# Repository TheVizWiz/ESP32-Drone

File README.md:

# ESP32 - Drone

### A Drone, Controller, and Flight Software, based on the popular ESP32 Microcontroller architecture.

## Current State
- Drone:  CAD model has been finalized and printed, as shown below. RF24 modules have been tested at distance, and motors and batteries have been mounted.
- Controller: PCB design is underway using multiplexers to extend ESP32 capabilities to more GPIO pins. RF24 module is being integrated, as well as battery circuitry.

### Drone Model

### PCB Schematic

## Overview
This is an ESP32-based from-scratch Drone project, meant to help learn the fundamentals of CAD, PCB design, control system software, as well as utilize the C++ programming language for high levels of multithreaded efficiency and performance. The Drone is built on a 4S cell system (14.8V), with 2200Kv motors (I would recommend going with a lower Kv value if you are reproducing this project, as that will be more efficient; I used what was on hand), and 10" propellers. It is designed to carry its own weight as well as a payload of ~1kg (2.2lb). 

## Project Objectives

### Drone
- Use Autodesk Inventor to design and 3D print a custom Drone body, built for carrying heavy weight (25+ kg).
- Utilize RF24 radio modules, as well as MPU6050 sensors, to build a real-time multithreaded flight control system, using PID control system algorithms.
- Create modular systems that allow for plug-and-play extension systems (eg. a payload-dropping and sensing system, as well as a front-mounted camera gimbal.)
- Build error-handling systems that allow for the easy handling of exception scenarios, such as loss of network signal or missed packets.
- Architecture system for Payload Acknowledge based telemetry, for use with flight telemetry / analysis software.

### Controller
- Use a secondary ESP32 system to measure input signals and relay to drone with RF24 modules.
- Utilize 74HC4051 ICs for breaking out signals, allowing for multiple expansion ports in the controller.
- Design and print controller body that allows for easy battery replacement and management, as well as easy access to controller ports for software updates. hook up GPIO_0 for easy boot access, as well as EN pin for reboots.

### Flight Software
- Use ElectronJS, ReactJS, and Victory Charts to create real-time telemetry for use on a desktop system.
- Build a Wifi-based connectivity system to relay information from drone to controller, package information, and then send asynchronously from controller to the host desktop system.
- Allow for multiple running systems and modes (sensing, graphs, console), as well as for reading data instead of only parsing from the drone. Further, use OpenGL and WebGL to render a 3D canvas view of the drone in flight.

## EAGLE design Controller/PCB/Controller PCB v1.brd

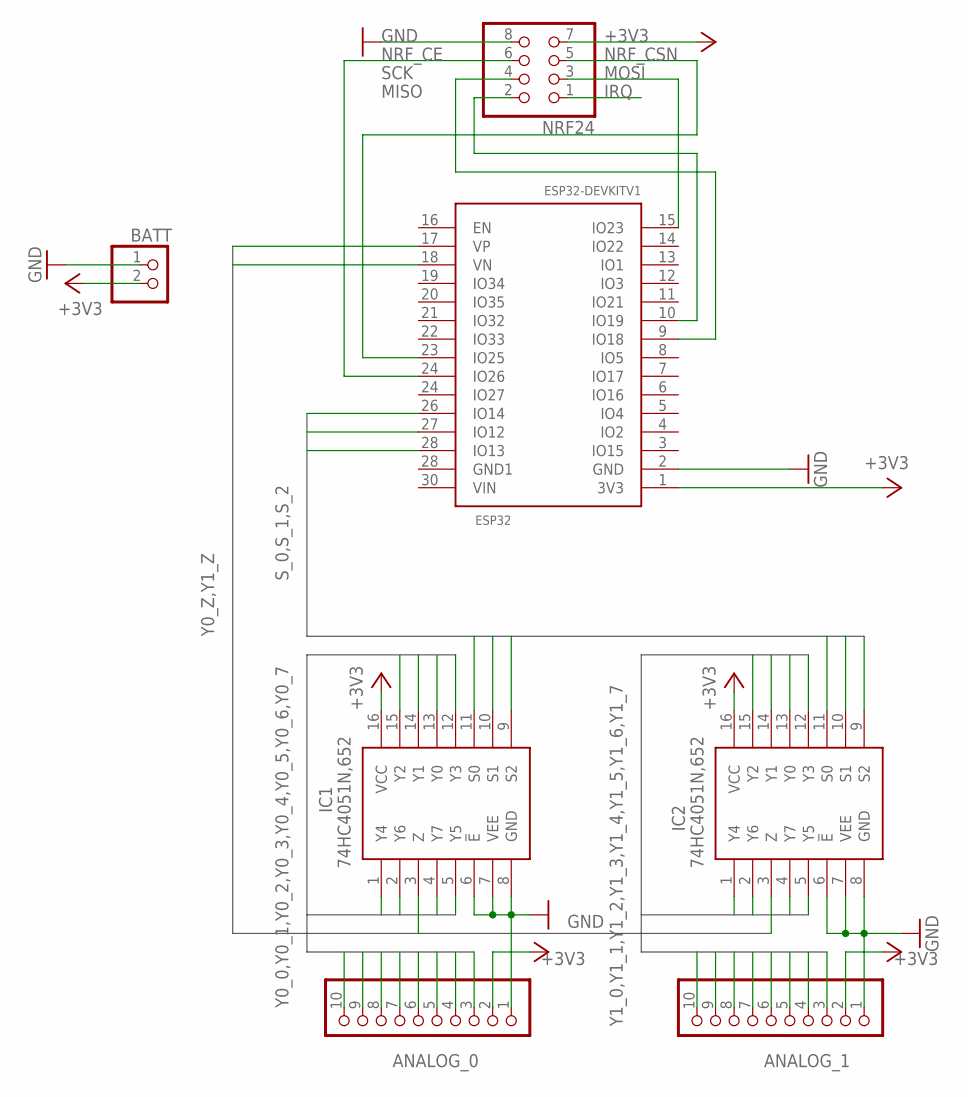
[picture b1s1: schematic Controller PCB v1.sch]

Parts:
ANALOG_0, ANALOG_1: PINHD-1X10/90; 1X10/90
BATT: PINHD-1X2; 1X02
ESP32: ESP32DEVKITV1; ESP32-DEVKITV1
IC1, IC2: 74HC4051N,652; DIP802W53P254L1902H420Q16N
NRF24: PINHD-2X4/90; 2X04/90

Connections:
+3V3: ANALOG_0.2, ANALOG_1.2, BATT.2, ESP32.1 (3V3), IC1.16 (VCC), IC2.16 (VCC), NRF24.7
GND: ANALOG_0.1, ANALOG_1.1, BATT.1, ESP32.2 (GND), IC1.6 (!E), IC1.7 (VEE), IC1.8 (GND), IC2.6 (!E), IC2.7 (VEE), IC2.8 (GND), NRF24.8
IRQ: NRF24.1
MISO: ESP32.10 (IO19), NRF24.2
MOSI: ESP32.15 (IO23), NRF24.3
NRF_CE: ESP32.24 (IO27), NRF24.6
NRF_CSN: ESP32.23 (IO25), NRF24.5
SCK: ESP32.9 (IO18), NRF24.4
S_0: ESP32.28 (IO13), IC1.11 (S0), IC2.11 (S0)
S_1: ESP32.27 (IO12), IC1.10 (S1), IC2.10 (S1)
S_2: ESP32.26 (IO14), IC1.9 (S2), IC2.9 (S2)
Y0_0: ANALOG_0.3, IC1.13 (Y0)
Y0_1: ANALOG_0.4, IC1.14 (Y1)
Y0_2: ANALOG_0.5, IC1.15 (Y2)
Y0_3: ANALOG_0.6, IC1.12 (Y3)
Y0_4: ANALOG_0.7, IC1.1 (Y4)
Y0_5: ANALOG_0.8, IC1.5 (Y5)
Y0_6: ANALOG_0.9, IC1.2 (Y6)
Y0_7: ANALOG_0.10, IC1.4 (Y7)
Y0_Z: ESP32.17 (VP), IC1.3 (Z)
Y1_0: ANALOG_1.3, IC2.13 (Y0)
Y1_1: ANALOG_1.4, IC2.14 (Y1)
Y1_2: ANALOG_1.5, IC2.15 (Y2)
Y1_3: ANALOG_1.6, IC2.12 (Y3)
Y1_4: ANALOG_1.7, IC2.1 (Y4)
Y1_5: ANALOG_1.8, IC2.5 (Y5)
Y1_6: ANALOG_1.9, IC2.2 (Y6)
Y1_7: ANALOG_1.10, IC2.4 (Y7)
Y1_Z: ESP32.18 (VN), IC2.3 (Z)

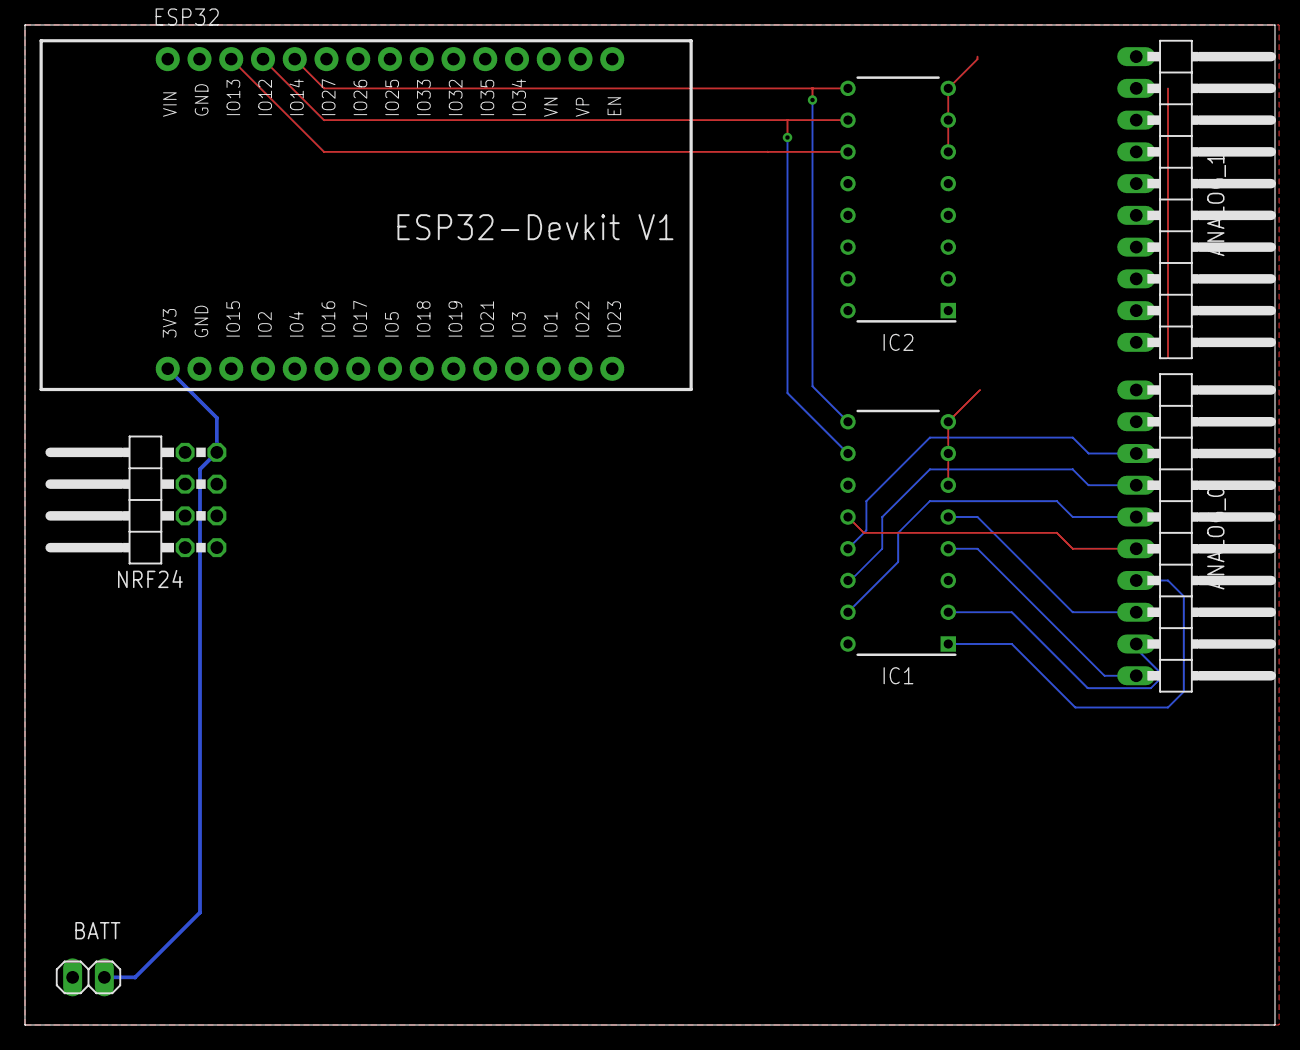
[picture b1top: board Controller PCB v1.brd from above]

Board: 2 copper layers, 100.0 x 80.0 mm, 7 parts (0 on the bottom side), 28 nets.

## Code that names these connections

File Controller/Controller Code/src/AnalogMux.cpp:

//
// Created by vibhu on 6/9/2022.
//

#include "AnalogMux.h"
#include "Arduino.h"


AnalogMux::AnalogMux (int s_0, int s_1, int s_2, int z) : AnalogMux(s_0, s_1, s_2, z, INPUT) {
}

AnalogMux::AnalogMux (int s_0, int s_1, int s_2, int z, int inputMode) {
	this->s_0 = s_0;
	this->s_1 = s_1;
	this->s_2 = s_2;
	this->z = z;
	pinMode(s_0, OUTPUT);
	pinMode(s_1, OUTPUT);
	pinMode(s_2, OUTPUT);
	pinMode(z, inputMode);

}

bool *AnalogMux::digitalReadAll () {
	bool reads[8];
	for (int i = 0; i < 8; ++i) {
		reads[i] = digitalRead(i);
	}
	return reads;
}

uint16_t *AnalogMux::analogReadAll () {
	uint16_t reads[8];
	for (int i = 0; i < 8; ++i) {
		setMux(i);
		reads[i] = Arduino_h::analogRead(z);
	}
	return reads;
}

void AnalogMux::setMux (int signalNumber) {
	digitalWrite(s_0, (signalNumber & 1) ? HIGH : LOW);
	digitalWrite(s_1, (signalNumber & 2) ? HIGH : LOW);
	digitalWrite(s_2, (signalNumber & 4) ? HIGH : LOW);
}

bool AnalogMux::digitalRead (int signalNumber) {
	setMux(signalNumber);
	return ::digitalRead(z);
}

uint16_t AnalogMux::analogRead (int signalNumber) {
	setMux(signalNumber);
	return ::analogRead(z);
}

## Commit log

2022-06-07 README update
2022-06-08 pcb work
2022-06-12 pcb work, controller code work
